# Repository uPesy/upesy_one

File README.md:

# uPesy One Board

In this repository you'll find Kicad 7.0 design files, BOM, schematics, 3D models for the uPesy One board. An Arduino UNO compatible board based on the ATMEGA328PB chip.

## 🙏 Contribute

Feel free to suggest improvements and report any bugs you encounter by submitting a PR or an issue :)

## ⚖️ License

The uPesy One board files are licensed under the [Creative Commons CC-BY-SA 4.0 License](https://creativecommons.org/licenses/by-sa/4.0/legalcode).

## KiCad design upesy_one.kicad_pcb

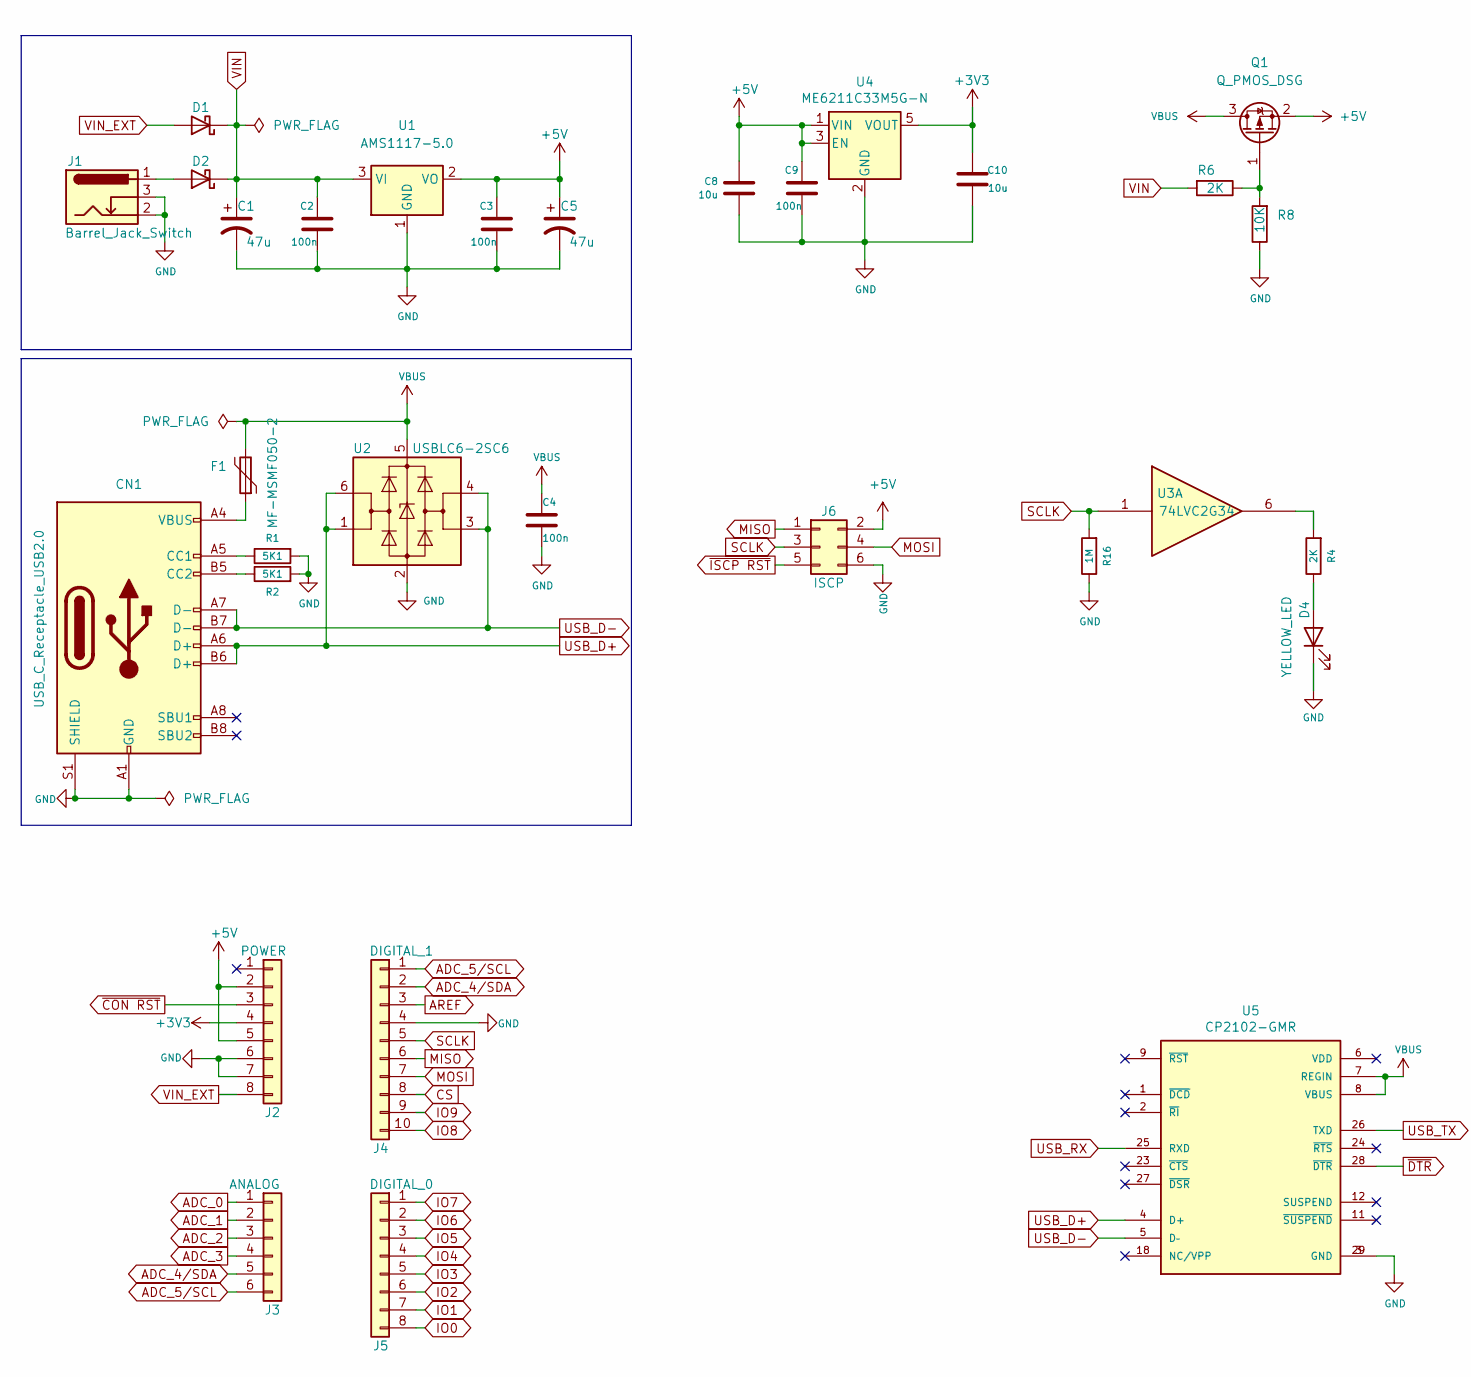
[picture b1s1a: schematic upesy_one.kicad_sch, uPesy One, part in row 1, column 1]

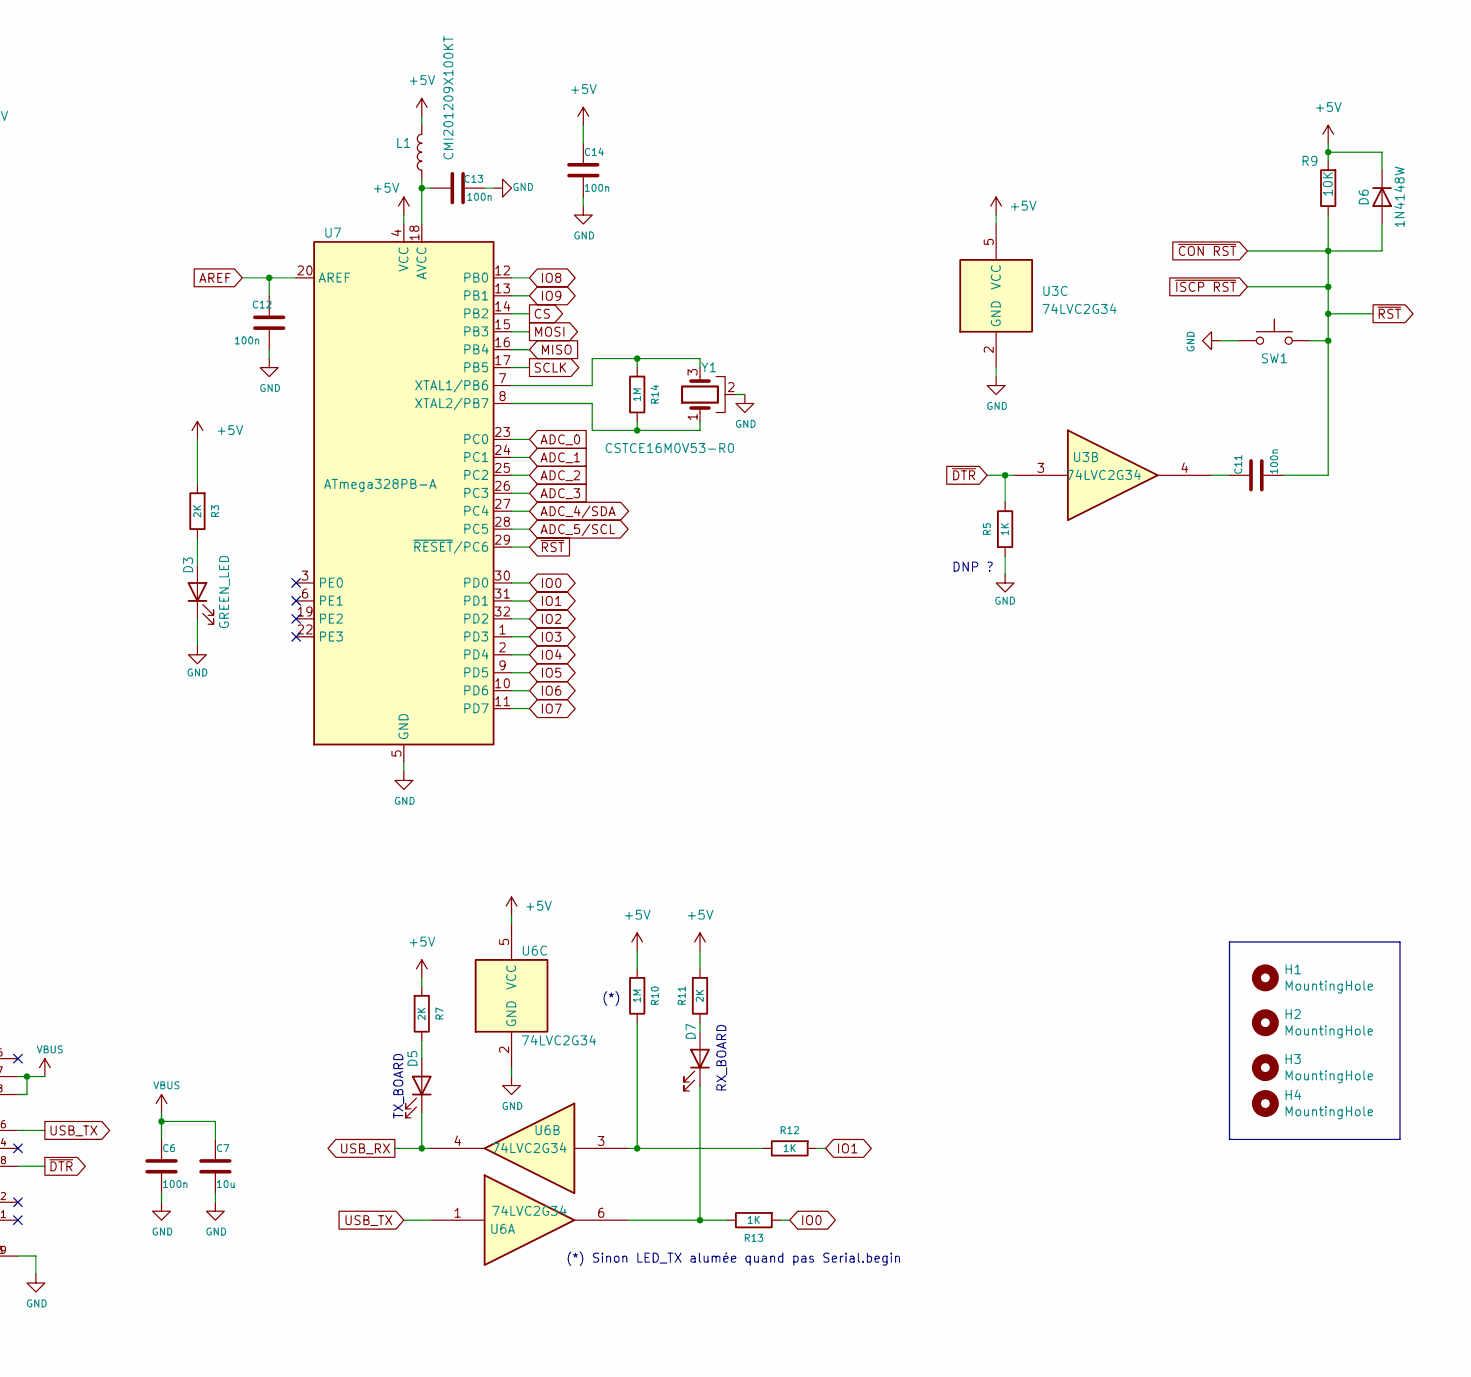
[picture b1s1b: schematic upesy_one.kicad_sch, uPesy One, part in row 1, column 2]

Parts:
C1, C5: 47u; CP_Elec_6.3x5.4
C2, C3, C4, C6, C9, C11, C12, C13, C14: 100n; C_0603_1608Metric
C7, C8, C10: 10u; C_0603_1608Metric
CN1: USB_C_Receptacle_USB2.0; USB_C_C165948
D1, D2: MBR120LSF; D_SOD-123
D3: GREEN_LED; LED_0603_1608Metric
D4, D5, D7: YELLOW_LED; LED_0603_1608Metric
D6: 1N4148W; D_SOD-123
F1: MF-MSMF050-2; R_1812_4532Metric
H1, H2, H3, H4: MountingHole; MountingHole_3.2mm_M3_DIN965
J1: Barrel_Jack_Switch; DC-IN_DC050-T
J2: POWER; PinSocket_1x08_P2.54mm_Vertical
J3: ANALOG; PinSocket_1x06_P2.54mm_Vertical
J4: DIGITAL_1; PinSocket_1x10_P2.54mm_Vertical
J5: DIGITAL_0; PinSocket_1x08_P2.54mm_Vertical
J6: ISCP; PinHeader_2x03_P2.54mm_Vertical
L1: CMI201209X100KT; L_0805_2012Metric
Q1: Q_PMOS_DSG; SOT-23
R1, R2: 5K1; R_0603_1608Metric
R3, R4, R6, R7, R11: 2K; R_0603_1608Metric
R5, R12, R13: 1K; R_0603_1608Metric
R8, R9: 10K; R_0603_1608Metric
R10, R14, R16: 1M; R_0603_1608Metric
SW1: SW_Push; KEY-SMD_4P-L4.5-W4.5-P3.00-LS6.9
U1: AMS1117-5.0; SOT-223-3_TabPin2
U2: USBLC6-2SC6; SOT-23-6
U3, U6: 74LVC2G34; SOT-363_SC-70-6
U4: ME6211C33M5G-N; SOT-23-5
U5: CP2102-GMR
U7: ATmega328PB-A; TQFP-32_7x7mm_P0.8mm
Y1: CSTCE16M0V53-R0; OSC-SMD_3P-L3.2-W1.3-P0.95-L

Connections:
+3V3: C10.2, J2.4, U4.5 (VOUT)
+5V: C3.1, C5.1, C8.2, C9.1, C14.2, D6.1 (K), J2.2, J2.5, J6.2, L1.2, Q1.2 (S), R3.2, R7.2, R9.2, R10.2, R11.2, U1.2 (VO), U3.5 (VCC), U4.1 (VIN), U4.3 (EN), U6.5 (VCC), U7.4 (VCC)
ADC_0: J3.1, U7.23 (PC0)
ADC_1: J3.2, U7.24 (PC1)
ADC_2: J3.3, U7.25 (PC2)
ADC_3: J3.4, U7.26 (PC3)
ADC_4/SDA: J3.5, J4.2, U7.27 (PC4)
ADC_5/SCL: J3.6, J4.1, U7.28 (PC5)
AREF: C12.2, J4.3, U7.20 (AREF)
CS: J4.8, U7.14 (PB2)
GND: C1.2, C2.2, C3.2, C4.1, C5.2, C6.1, C7.2, C8.1, C9.2, C10.1, C12.1, C13.2, C14.1, CN1.A1 (GND), CN1.A12 (GND), CN1.S1 (SHIELD), D3.1 (K), D4.1 (K), J1.2, J1.3, J2.6, J2.7, J4.4, J6.6, R1.2, R2.2, R5.2, R8.1, R16.1, SW1.1, U1.1 (GND), U2.2 (GND), U3.2 (GND), U4.2 (GND), U5.3 (GND), U5.29 (GND), U6.2 (GND), U7.5 (GND), U7.21 (GND), Y1.2
IO0: J5.8, R13.2, U7.30 (PD0)
IO1: J5.7, R12.2, U7.31 (PD1)
IO2: J5.6, U7.32 (PD2)
IO3: J5.5, U7.1 (PD3)
IO4: J5.4, U7.2 (PD4)
IO5: J5.3, U7.9 (PD5)
IO6: J5.2, U7.10 (PD6)
IO7: J5.1, U7.11 (PD7)
IO8: J4.10, U7.12 (PB0)
IO9: J4.9, U7.13 (PB1)
MISO: J4.6, J6.1, U7.16 (PB4)
MOSI: J4.7, J6.4, U7.15 (PB3)
unnamed: C11.2, U3.4
unnamed: CN1.A5 (CC1), R1.1
unnamed: CN1.B5 (CC2), R2.1
unnamed: CN1.A4 (VBUS), CN1.A9 (VBUS), F1.1
unnamed: D2.2 (A), J1.1
unnamed: D3.2 (A), R3.1
unnamed: D4.2 (A), R4.1
unnamed: D5.2 (A), R7.1
unnamed: D7.2 (A), R11.1
unnamed: D7.1 (K), R13.1, U6.6
unnamed: Q1.1 (G), R6.1, R8.2
unnamed: R4.2, U3.6
unnamed: R10.1, R12.1, U6.3
unnamed: C13.1, L1.1, U7.18 (AVCC)
unnamed: R14.2, U7.7 (XTAL1/PB6), Y1.3
unnamed: R14.1, U7.8 (XTAL2/PB7), Y1.1
SCLK: J4.5, J6.3, R16.2, U3.1, U7.17 (PB5)
USB_D+: CN1.A6 (D+), CN1.B6 (D+), U2.1 (I/O1), U2.6 (I/O1), U5.4 (D+)
USB_D-: CN1.A7 (D-), CN1.B7 (D-), U2.3 (I/O2), U2.4 (I/O2), U5.5 (D–)
USB_RX: D5.1 (K), U5.25 (RXD), U6.4
USB_TX: U5.26 (TXD), U6.1
VBUS: C4.2, C6.2, C7.1, F1.2, Q1.3 (D), U2.5 (VBUS), U5.7 (REGIN), U5.8 (VBUS)
VIN: C1.1, C2.1, D1.1 (K), D2.1 (K), R6.2, U1.3 (VI)
VIN_EXT: D1.2 (A), J2.8
~CON RST: C11.1, D6.2 (A), J2.3, J6.5, R9.1, SW1.2, U7.29 (~RESET/PC6)
~DTR: R5.1, U3.3, U5.28 (~DTR)

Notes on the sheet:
TX_BOARD
(*) Sinon LED_TX alumée quand pas Serial.begin
RX_BOARD
(*)
DNP ?

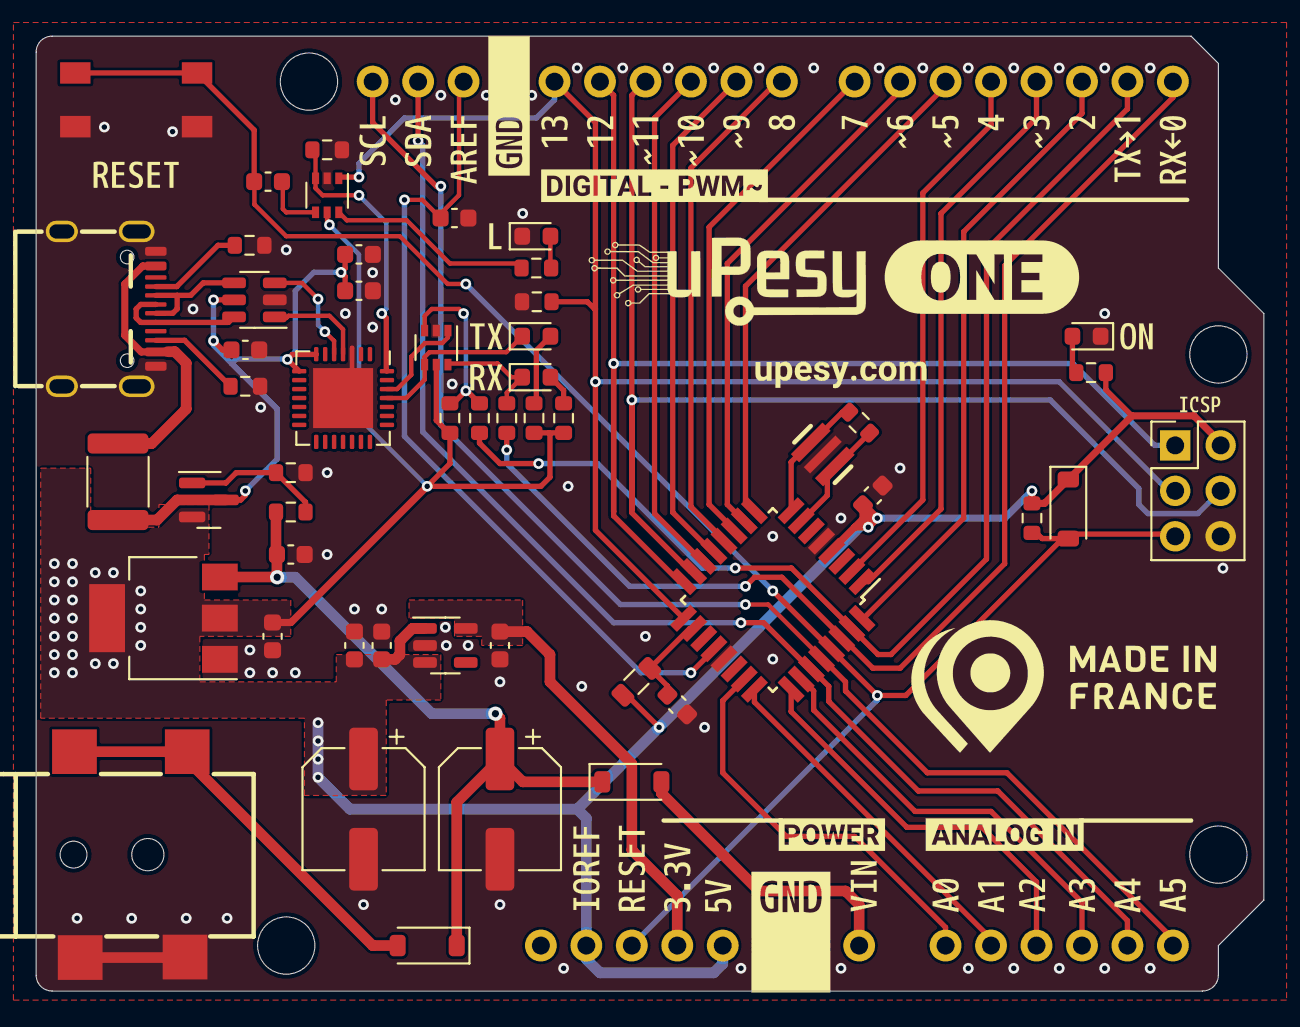
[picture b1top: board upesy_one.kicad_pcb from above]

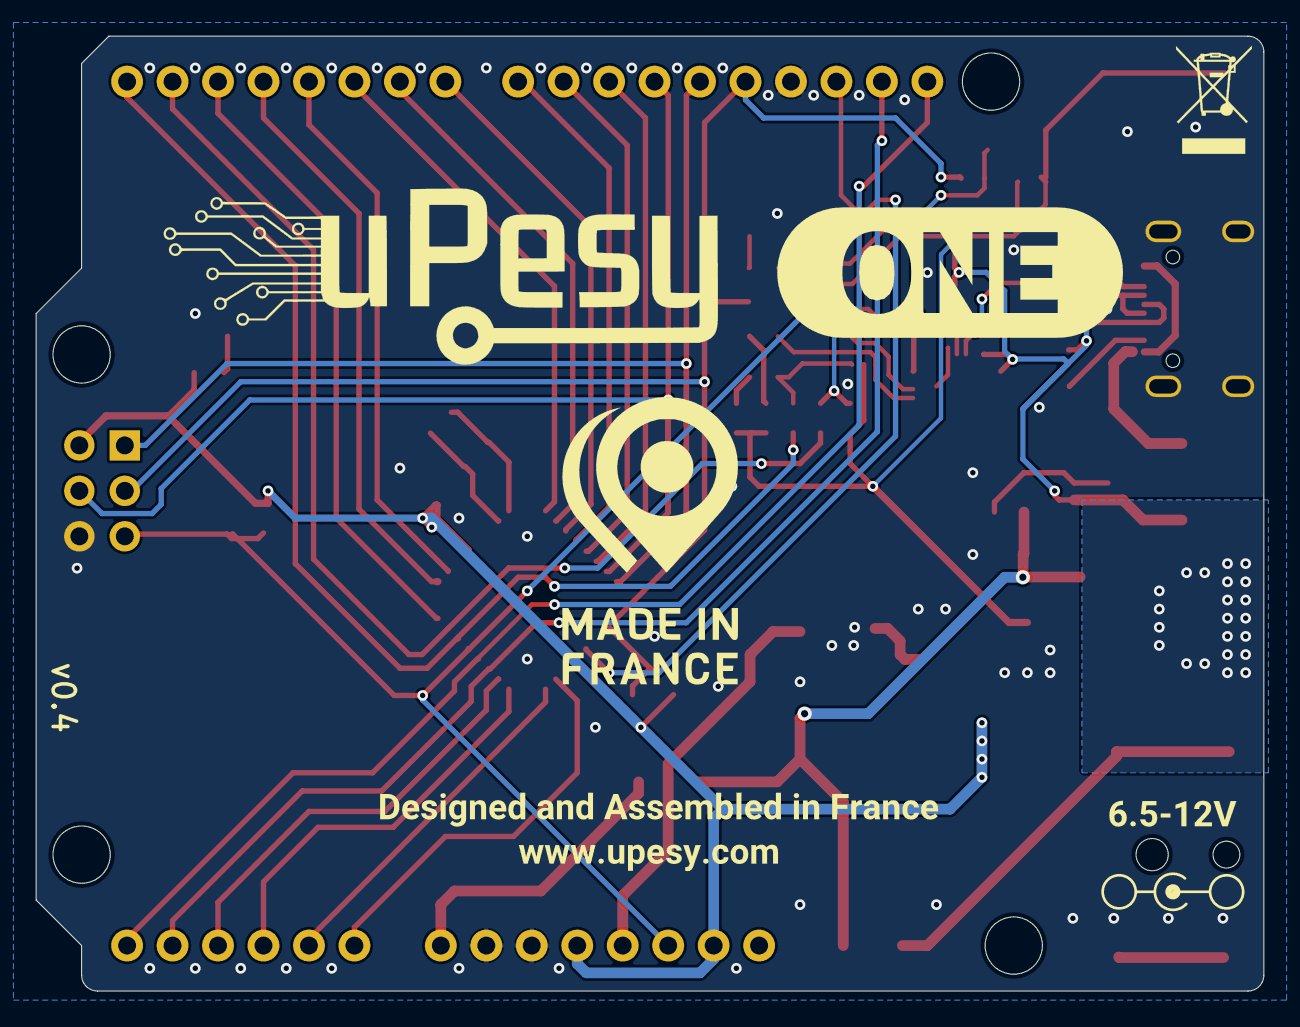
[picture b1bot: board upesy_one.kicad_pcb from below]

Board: 2 copper layers, 68.6 x 53.3 mm, 103 parts (3 on the bottom side), 49 nets.

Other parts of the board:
kibuzzard-63D7D00B: G***; kibuzzard-63D7D00B
kibuzzard-63D7D0BF: G***; kibuzzard-63D7D0BF
kibuzzard-63D7D0D3: G***; kibuzzard-63D7D0D3
kibuzzard-63D7D0E6: G***; kibuzzard-63D7D0E6
kibuzzard-63D7D0F3: G***; kibuzzard-63D7D0F3
kibuzzard-63D7D0F8: G***; kibuzzard-63D7D0F8
kibuzzard-63D7D1B7: G***; kibuzzard-63D7D1B7
kibuzzard-63D7D1D2: G***; kibuzzard-63D7D1D2
kibuzzard-63D7D01F: G***; kibuzzard-63D7D01F
kibuzzard-63D7D2C3: G***; kibuzzard-63D7D2C3
kibuzzard-63D7D2CB: G***; kibuzzard-63D7D2CB
kibuzzard-63D7D2D1: G***; kibuzzard-63D7D2D1
kibuzzard-63D7D2F8: G***; kibuzzard-63D7D2F8
kibuzzard-63D7D3AA: G***; kibuzzard-63D7D3AA
kibuzzard-63D7D3C4: G***; kibuzzard-63D7D3C4
kibuzzard-63D7D3CA: G***; kibuzzard-63D7D3CA
kibuzzard-63D7D04D: G***; kibuzzard-63D7D04D
kibuzzard-63D7D22A: G***; kibuzzard-63D7D22A
kibuzzard-63D7D32A: G***; kibuzzard-63D7D32A
kibuzzard-63D7D060: G***; kibuzzard-63D7D060
kibuzzard-63D7D69A: G***; kibuzzard-63D7D69A
kibuzzard-63D7D81F: G***; kibuzzard-63D7D81F
kibuzzard-63D7D84E: G***; kibuzzard-63D7D84E
kibuzzard-63D7D183: G***; kibuzzard-63D7D183
kibuzzard-63D7D199: G***; kibuzzard-63D7D199
kibuzzard-63D7D238: G***; kibuzzard-63D7D238
kibuzzard-63D7D324: G***; kibuzzard-63D7D324
kibuzzard-63D7D772: G***; kibuzzard-63D7D772
kibuzzard-63D7D845: G***; kibuzzard-63D7D845
kibuzzard-63D7D852: G***; kibuzzard-63D7D852
kibuzzard-63D7DA83: G***; kibuzzard-63D7DA83
kibuzzard-63D7DCFF: G***; kibuzzard-63D7DCFF
kibuzzard-63D7DD21: G***; kibuzzard-63D7DD21
kibuzzard-63D7DF6C: G***; kibuzzard-63D7DF6C
kibuzzard-63D7DFCE: G***; kibuzzard-63D7DFCE
kibuzzard-63DA85A6: G***; kibuzzard-63DA85A6
kibuzzard-63DA865D: G***; kibuzzard-63DA865D
kibuzzard-642FC67E: G***; kibuzzard-642FC67E
kibuzzard-642FC77B: G***; kibuzzard-642FC77B
kibuzzard-642FC531: G***; kibuzzard-642FC531
kibuzzard-6411EABE: G***; kibuzzard-6411EABE
kibuzzard-6464A8D9: G***; kibuzzard-6464A8D9
kibuzzard-64300AB8: G***; kibuzzard-64300AB8
kibuzzard-643009C9: G***; kibuzzard-643009C9

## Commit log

2023-06-21 init repo

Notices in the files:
upesy_one.kicad_sch:
This file is licensed under CC-BY-SA-4.0
